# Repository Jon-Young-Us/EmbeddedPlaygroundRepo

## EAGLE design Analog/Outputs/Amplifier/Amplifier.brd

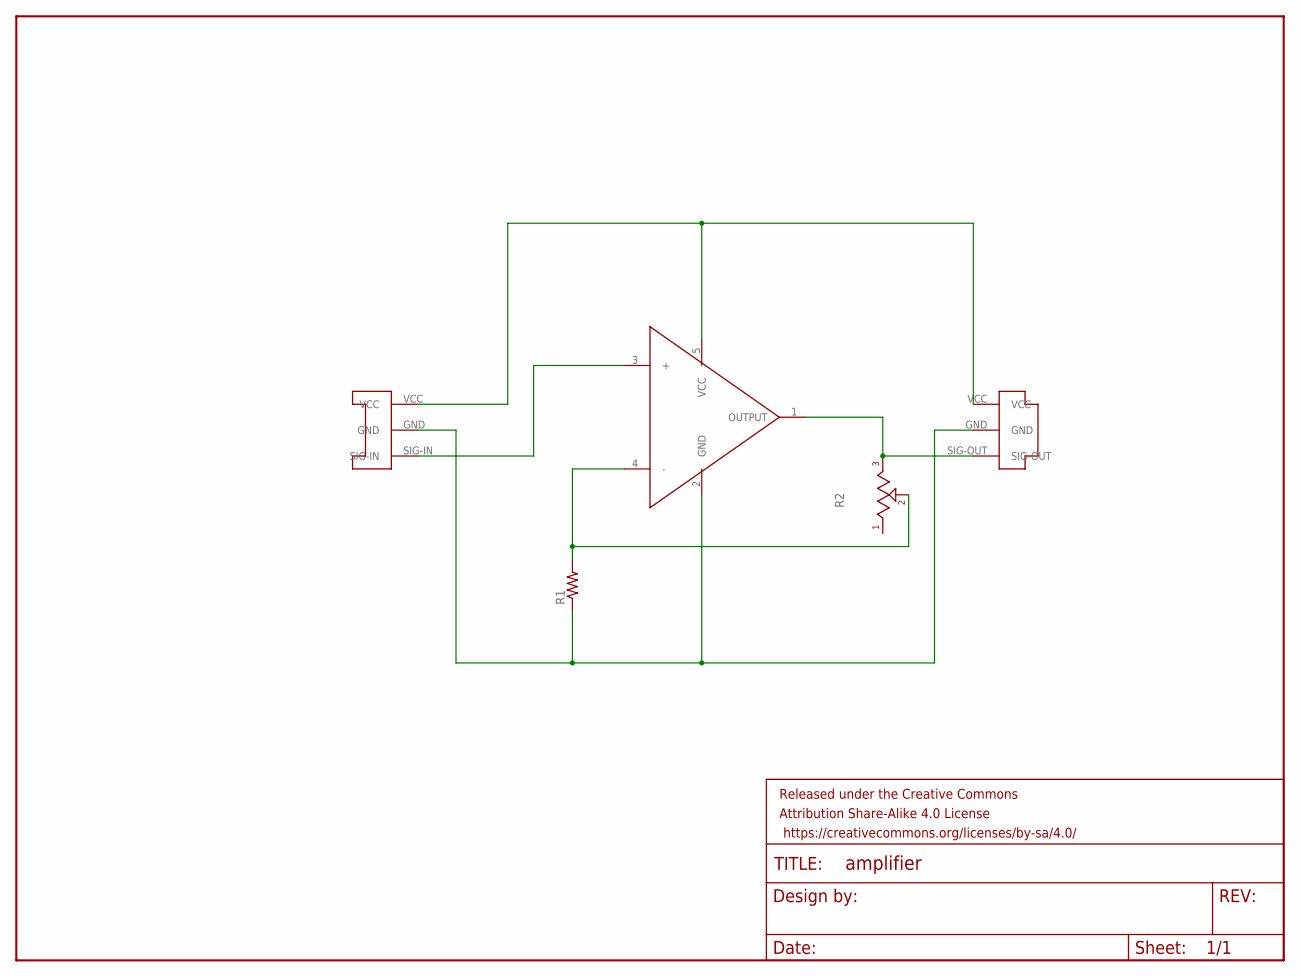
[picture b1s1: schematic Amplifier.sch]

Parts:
FRAME1: FRAME-LETTERNO_PACKAGE; DUMMY
R1: RESISTOR0603; 0603-RES
R2: POT-TRIM-SMD-BOURNS-3314J-1; POT-TRIM-SMD-BOURNS-3314
U$1: CONN-PLUG-3POS-3MM; PLUG-3POS-3MM-SMD
U$2: CONN-SOCKET-3POS-3MM; SOCKET-3POS-3MM-SMD
U$3: OPAMP-MCP6001SC70-5; SC70

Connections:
GND: R1.1, U$1.GND, U$2.GND, U$3.2 (GND)
unnamed: U$2.SIG-IN, U$3.3 (+)
unnamed: R1.2, R2.2, U$3.4 (-)
unnamed: R2.1 (3), U$1.SIG-OUT, U$3.1 (OUTPUT)
VCC: U$1.VCC, U$2.VCC, U$3.5 (VCC)

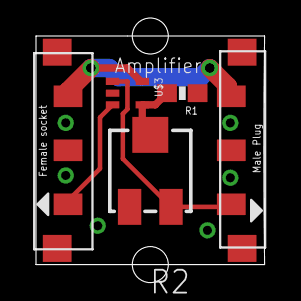
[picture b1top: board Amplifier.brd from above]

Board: 2 copper layers, 12.7 x 12.7 mm, 6 parts (0 on the bottom side), 5 nets.

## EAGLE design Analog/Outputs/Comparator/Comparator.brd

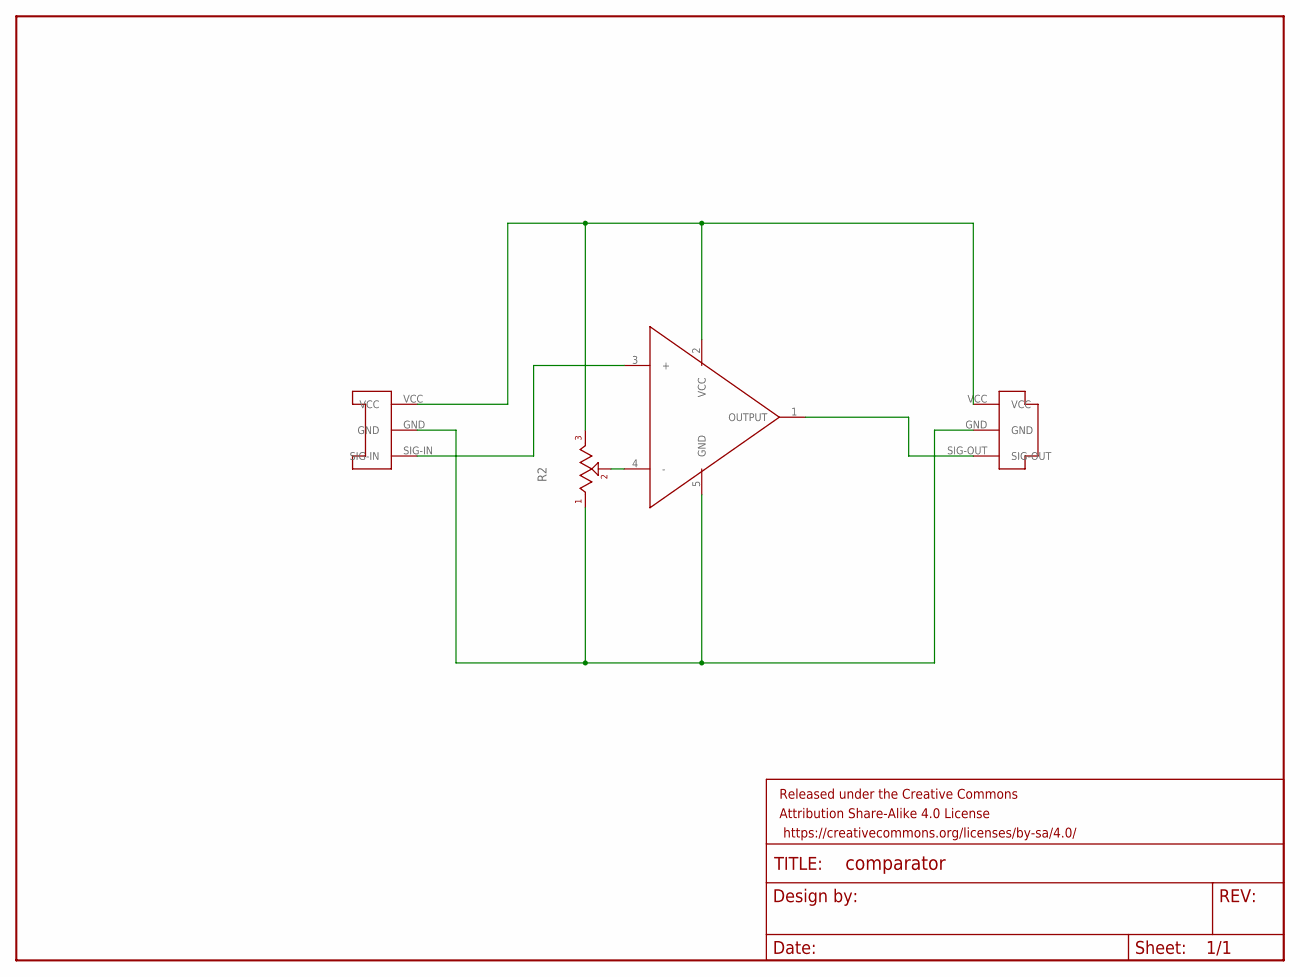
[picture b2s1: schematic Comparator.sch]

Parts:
FRAME1: FRAME-LETTERNO_PACKAGE; DUMMY
R2: POT-TRIM-SMD-BOURNS-3314J-1; POT-TRIM-SMD-BOURNS-3314
U$1: CONN-PLUG-3POS-3MM; PLUG-3POS-3MM-SMD
U$2: CONN-SOCKET-3POS-3MM; SOCKET-3POS-3MM-SMD
U$3: COMPARATOR-NCS2200; SOT23-5

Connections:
GND: R2.3 (1), U$1.GND, U$2.GND, U$3.5 (GND)
unnamed: U$2.SIG-IN, U$3.3 (+)
unnamed: R2.2, U$3.4 (-)
unnamed: U$1.SIG-OUT, U$3.1 (OUTPUT)
VCC: R2.1 (3), U$1.VCC, U$2.VCC, U$3.2 (VCC)

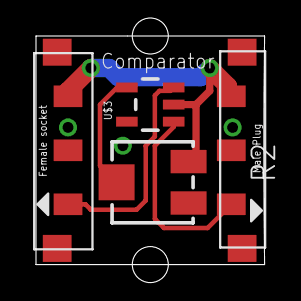
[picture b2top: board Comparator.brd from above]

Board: 2 copper layers, 12.7 x 12.7 mm, 5 parts (0 on the bottom side), 5 nets.

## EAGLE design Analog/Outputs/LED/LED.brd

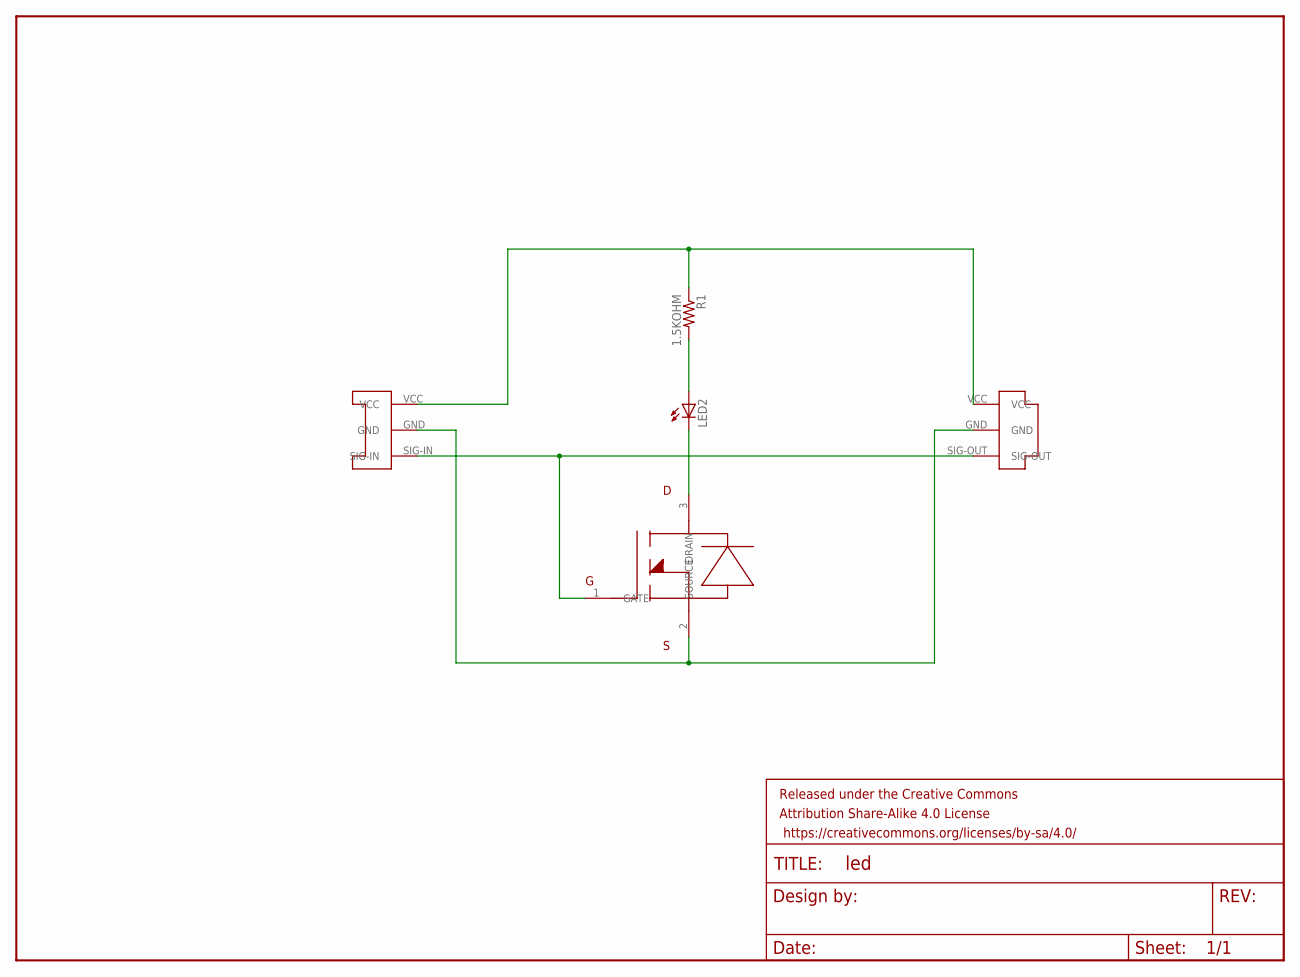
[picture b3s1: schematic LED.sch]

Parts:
FRAME1: FRAME-LETTERNO_PACKAGE; DUMMY
LED2: LEDCHIPLED_1206; CHIPLED_1206
R1: 1.5KOHM; 0603
U$1: CONN-PLUG-3POS-3MM; PLUG-3POS-3MM-SMD
U$2: CONN-SOCKET-3POS-3MM; SOCKET-3POS-3MM-SMD
U$3: MOSFET-N-CHAN; SOT23-3

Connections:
GND: U$1.GND, U$2.GND, U$3.2 (SOURCE)
unnamed: LED2.A, R1.2
unnamed: LED2.C, U$3.3 (DRAIN)
SIG: U$1.SIG-OUT, U$2.SIG-IN, U$3.1 (GATE)
VCC: R1.1, U$1.VCC, U$2.VCC

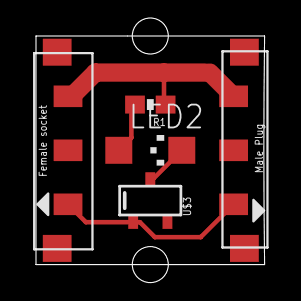
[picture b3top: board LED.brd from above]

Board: 2 copper layers, 12.7 x 12.7 mm, 6 parts (0 on the bottom side), 5 nets.

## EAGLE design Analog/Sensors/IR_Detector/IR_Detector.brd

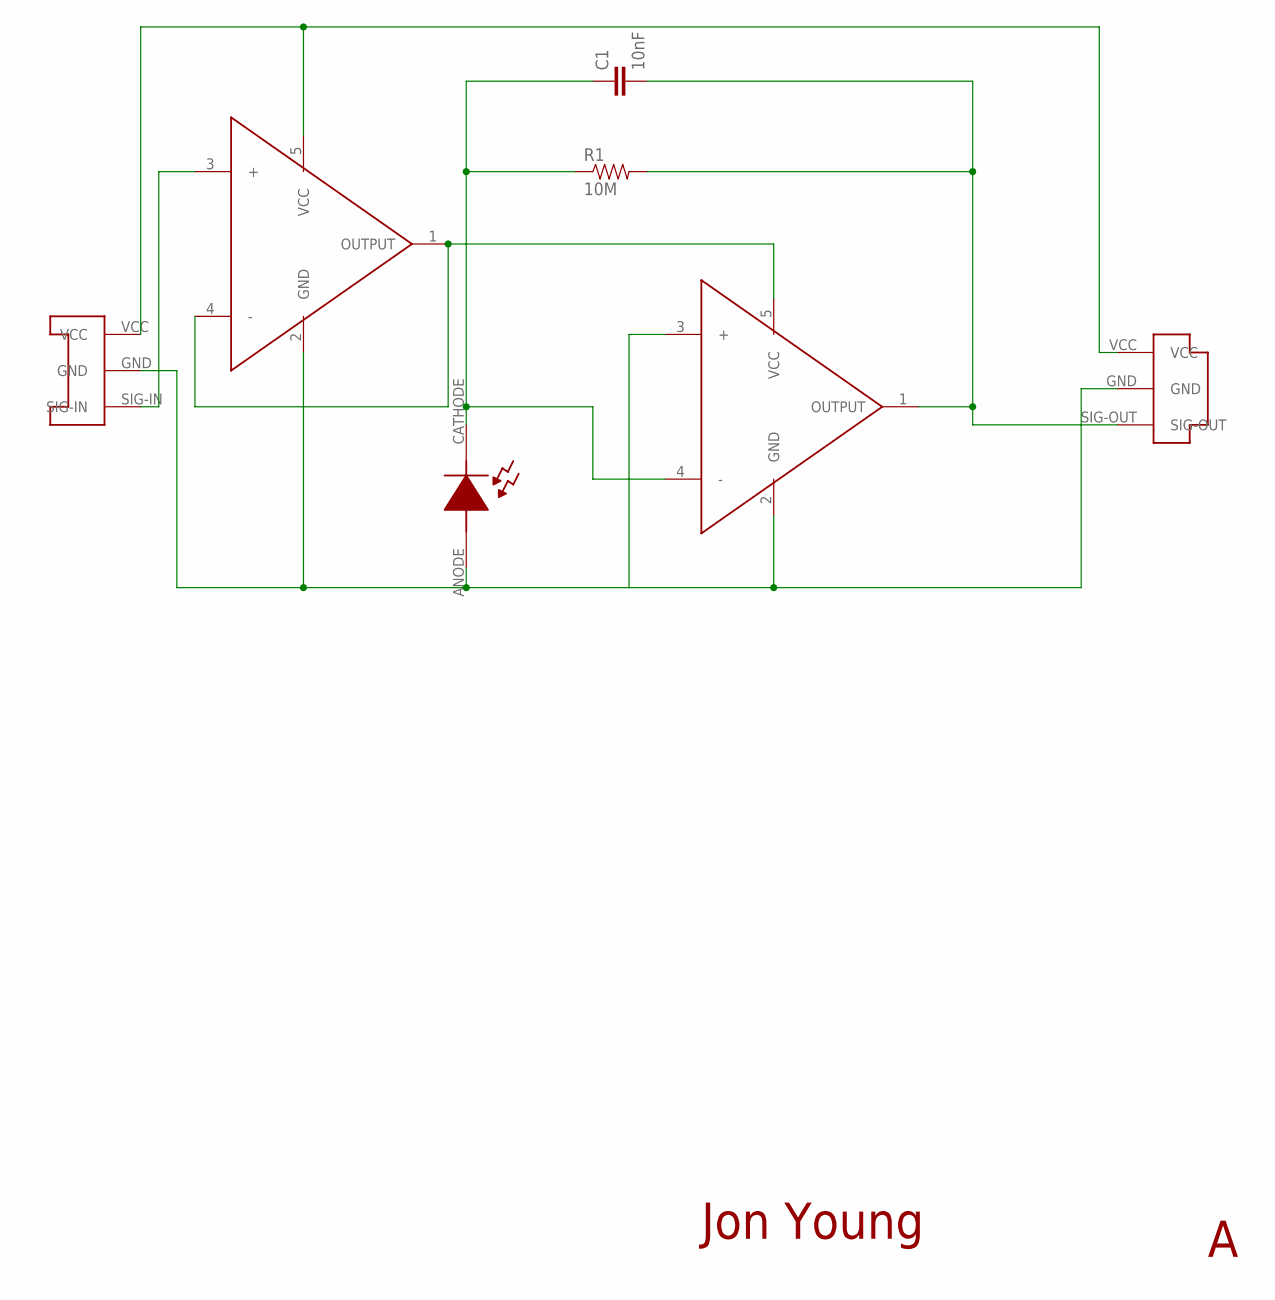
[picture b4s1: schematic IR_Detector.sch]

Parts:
C1: 10nF; 0603-CAP
R1: 10M; 0603-RES
U$1: CONN-PLUG-3POS-3MM; PLUG-3POS-3MM-SMD
U$2: CONN-SOCKET-3POS-3MM; SOCKET-3POS-3MM-SMD
U$3: VEMD2020; VEMD2020X01
U$4, U$5: OPAMP-MCP6001SC70-5; SC70

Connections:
GND: U$1.GND, U$2.GND, U$3.ANODE, U$4.2 (GND), U$4.3 (+), U$5.2 (GND)
unnamed: U$2.SIG-IN, U$5.3 (+)
unnamed: C1.1, R1.1, U$3.CATHODE, U$4.4 (-)
unnamed: U$4.5 (VCC), U$5.1 (OUTPUT), U$5.4 (-)
SIG-OUT: C1.2, R1.2, U$1.SIG-OUT, U$4.1 (OUTPUT)
VCC: U$1.VCC, U$2.VCC, U$5.5 (VCC)

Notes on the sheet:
Jon Young

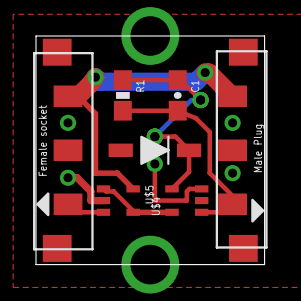
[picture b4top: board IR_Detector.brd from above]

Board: 2 copper layers, 12.7 x 12.7 mm, 7 parts (0 on the bottom side), 6 nets.

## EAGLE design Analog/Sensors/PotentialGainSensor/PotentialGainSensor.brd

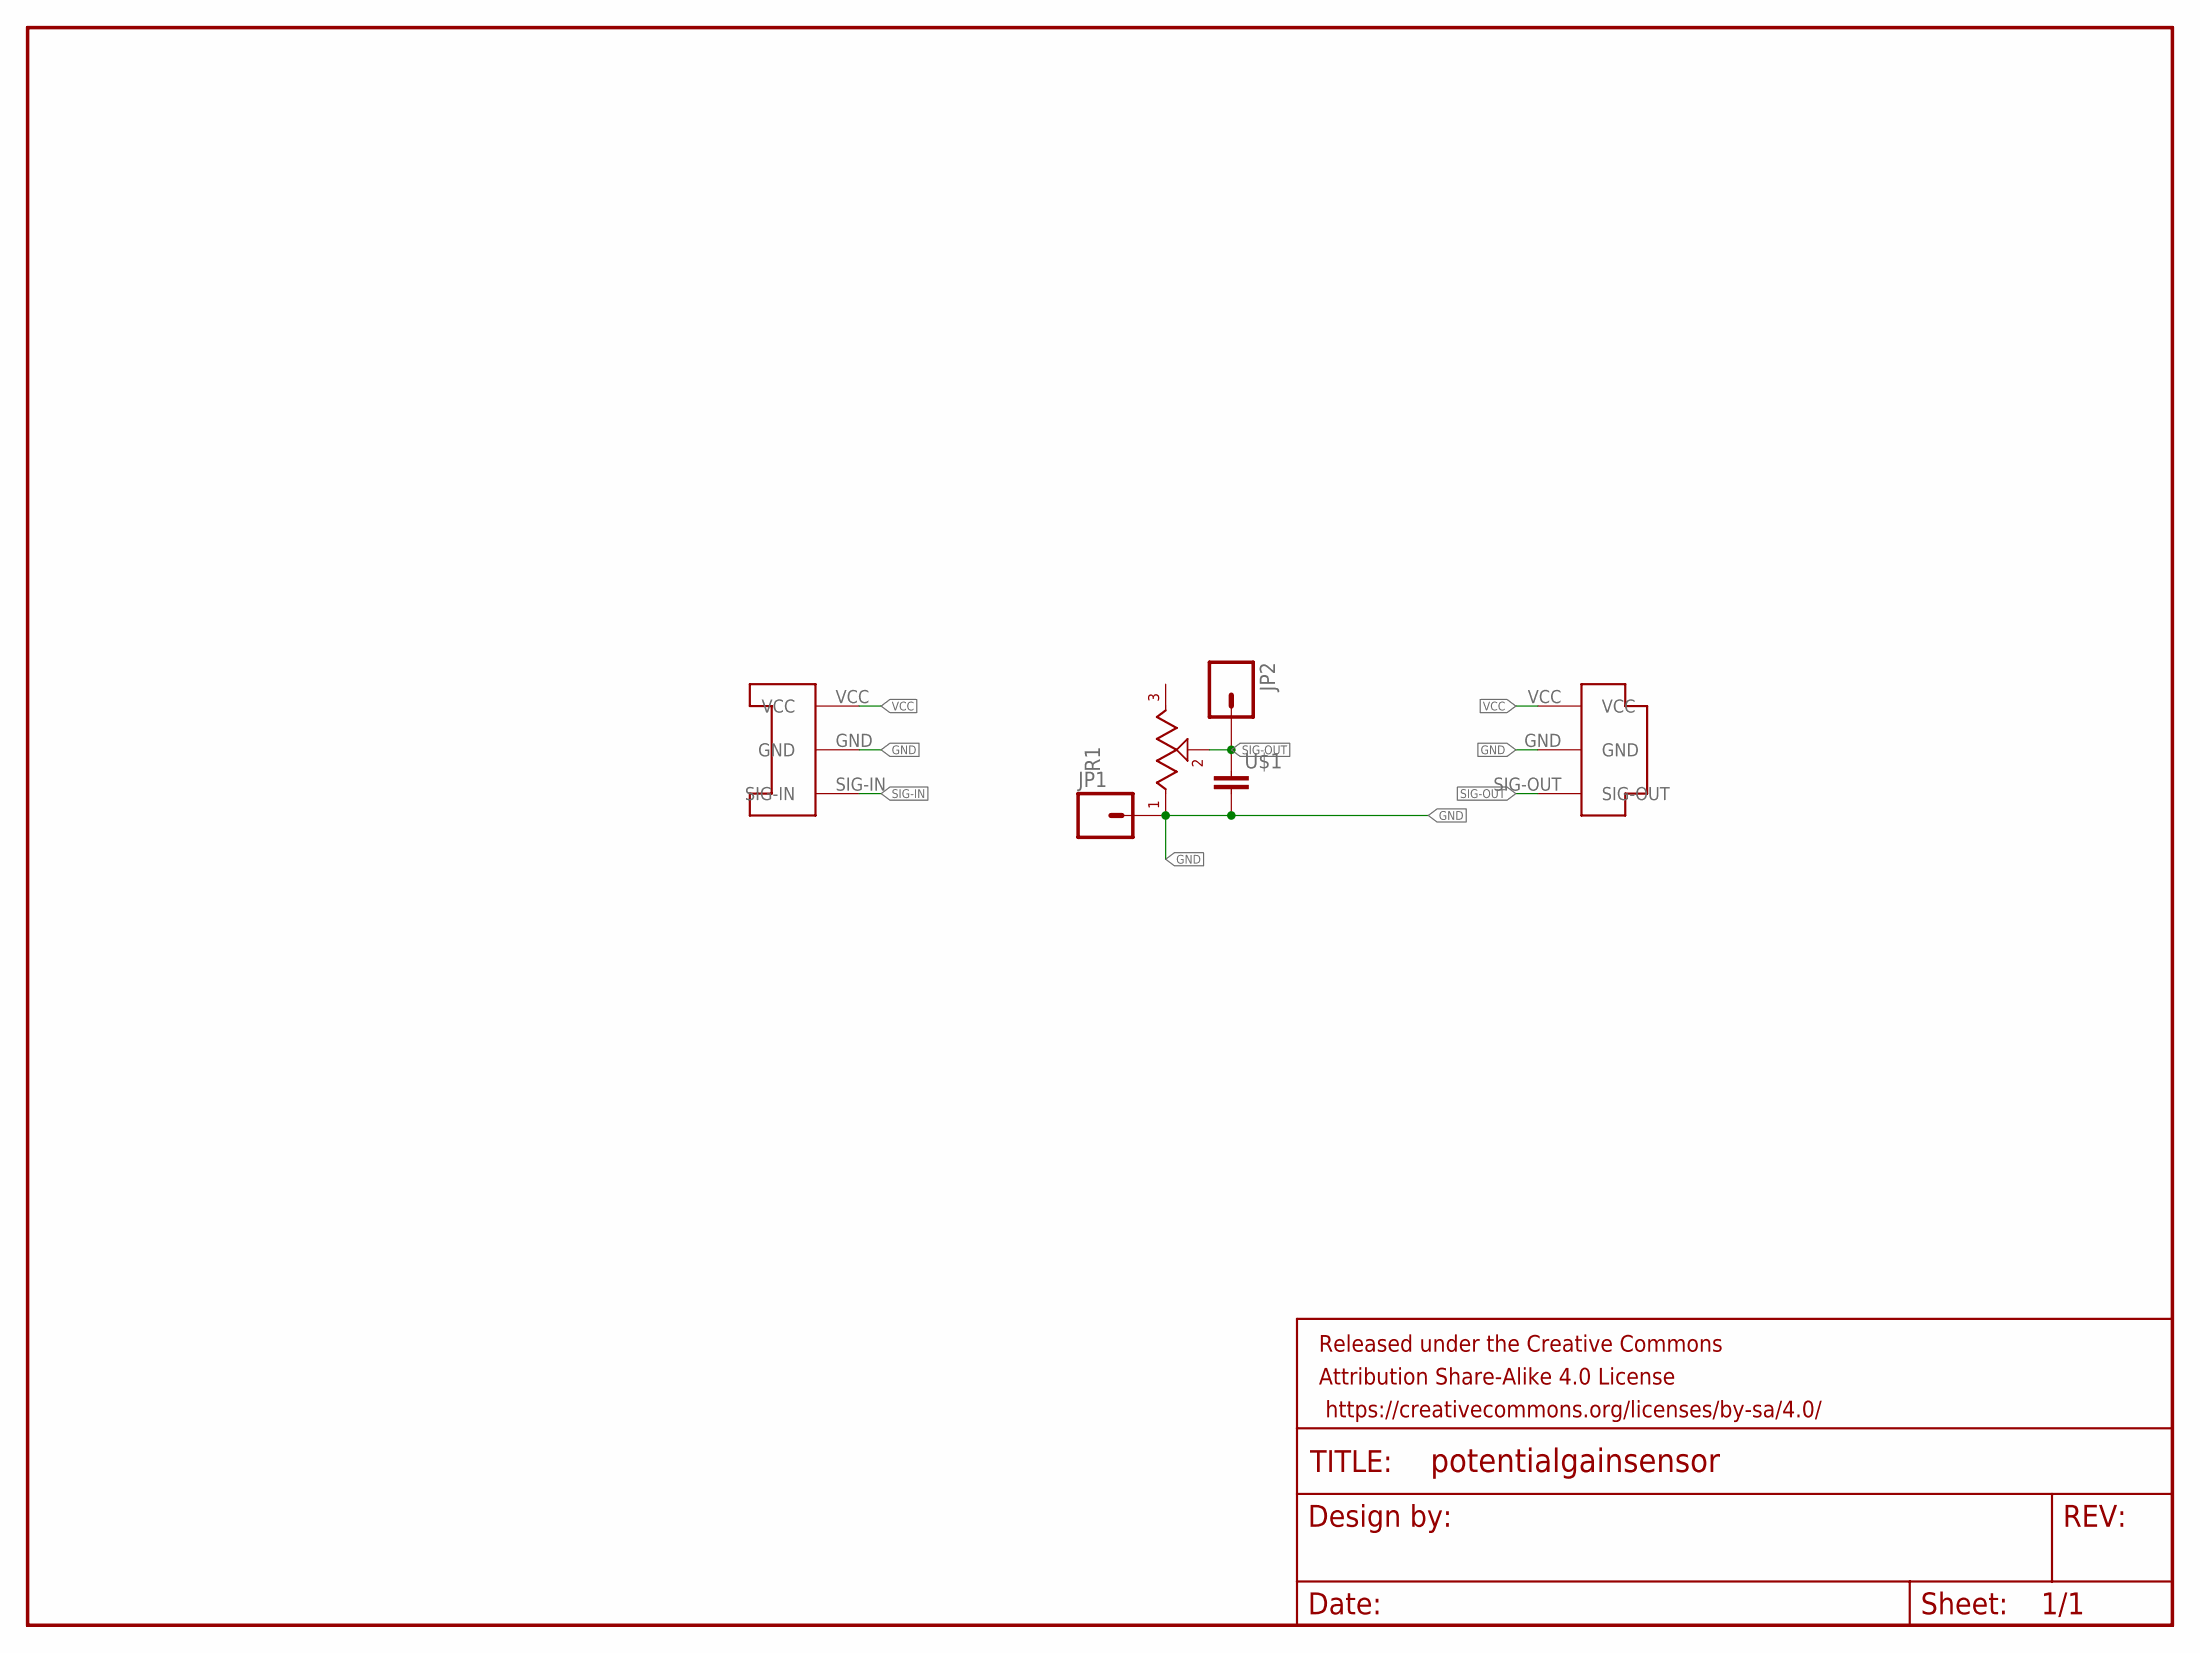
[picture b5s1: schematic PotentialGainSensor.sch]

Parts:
FRAME1: FRAME-LETTERNO_PACKAGE; DUMMY
JP1, JP2: M01SPRING-CONN; SPRING-CONNECTOR
R1: POT-TRIM-SMD-BOURNS-3314J-1; POT-TRIM-SMD-BOURNS-3314
U$1: CAPCAP-0805; CAP-0805
U$2: CONN-PLUG-3POS-3MM; PLUG-3POS-3MM-SMD
U$3: CONN-SOCKET-3POS-3MM; SOCKET-3POS-3MM-SMD

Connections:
GND: JP1.P$2, R1.3 (1), U$1.2, U$2.GND, U$3.GND
SIG-IN: U$3.SIG-IN
SIG-OUT: JP2.P$2, R1.2, U$1.1, U$2.SIG-OUT
VCC: U$2.VCC, U$3.VCC

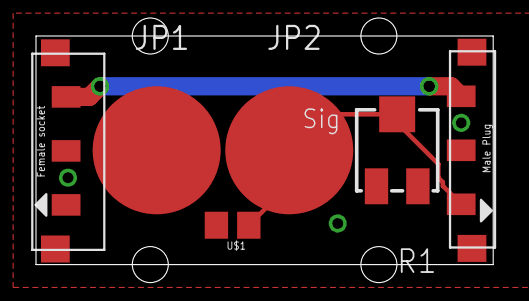
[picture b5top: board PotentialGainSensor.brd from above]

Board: 2 copper layers, 25.4 x 12.7 mm, 7 parts (0 on the bottom side), 3 nets.

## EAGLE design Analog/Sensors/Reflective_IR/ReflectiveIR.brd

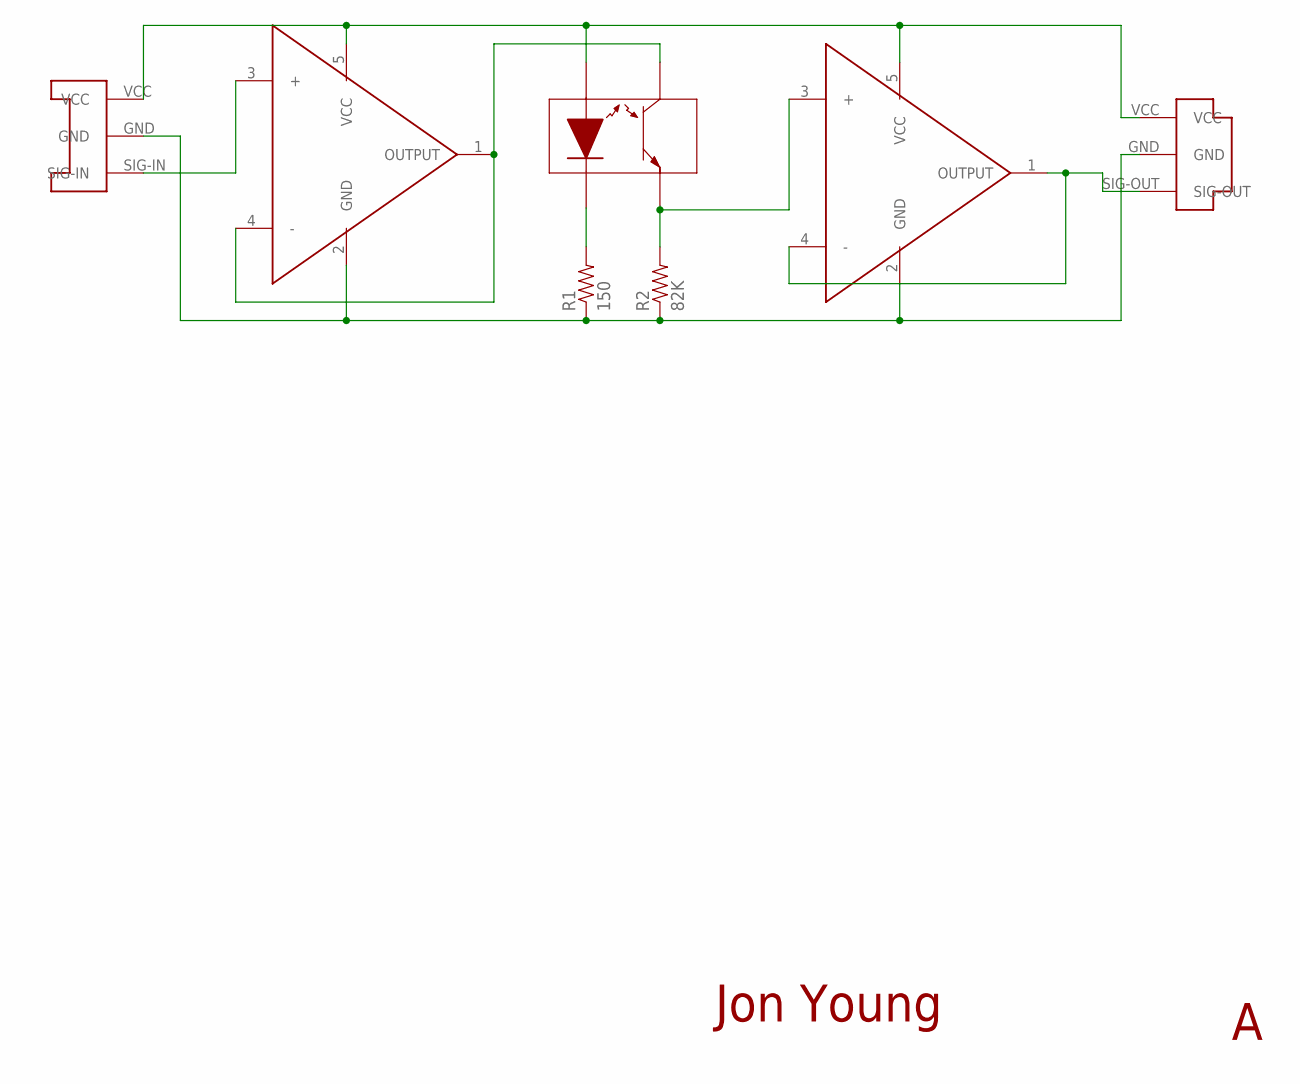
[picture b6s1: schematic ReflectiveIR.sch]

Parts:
R1: 150; 0603-RES
R2: 82K; 0603-RES
U$1: CONN-PLUG-3POS-3MM; PLUG-3POS-3MM-SMD
U$2: CONN-SOCKET-3POS-3MM; SOCKET-3POS-3MM-SMD
U$3: REFLECTIVE-SENSOR-OPB733TR
U$4, U$5: OPAMP-MCP6001SC70-5; SC70

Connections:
GND: R1.1, R2.1, U$1.GND, U$2.GND, U$4.2 (GND), U$5.2 (GND)
unnamed: R2.2, U$3.P2-EMITTER, U$5.3 (+)
unnamed: R1.2, U$3.P1-CATHODE
unnamed: U$3.P3-COLLECTOR, U$4.1 (OUTPUT), U$4.4 (-)
unnamed: U$2.SIG-IN, U$4.3 (+)
SIG-OUT: U$1.SIG-OUT, U$5.1 (OUTPUT), U$5.4 (-)
VCC: U$1.VCC, U$2.VCC, U$3.P4-ANODE, U$4.5 (VCC), U$5.5 (VCC)

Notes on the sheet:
Jon Young

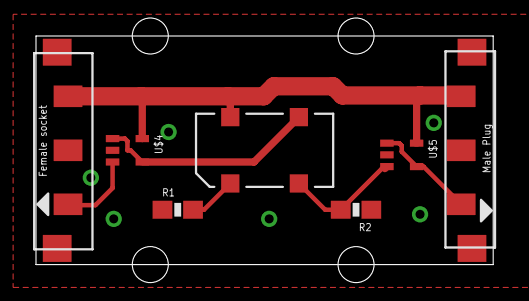
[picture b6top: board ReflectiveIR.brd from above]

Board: 2 copper layers, 25.4 x 12.7 mm, 7 parts (0 on the bottom side), 7 nets.

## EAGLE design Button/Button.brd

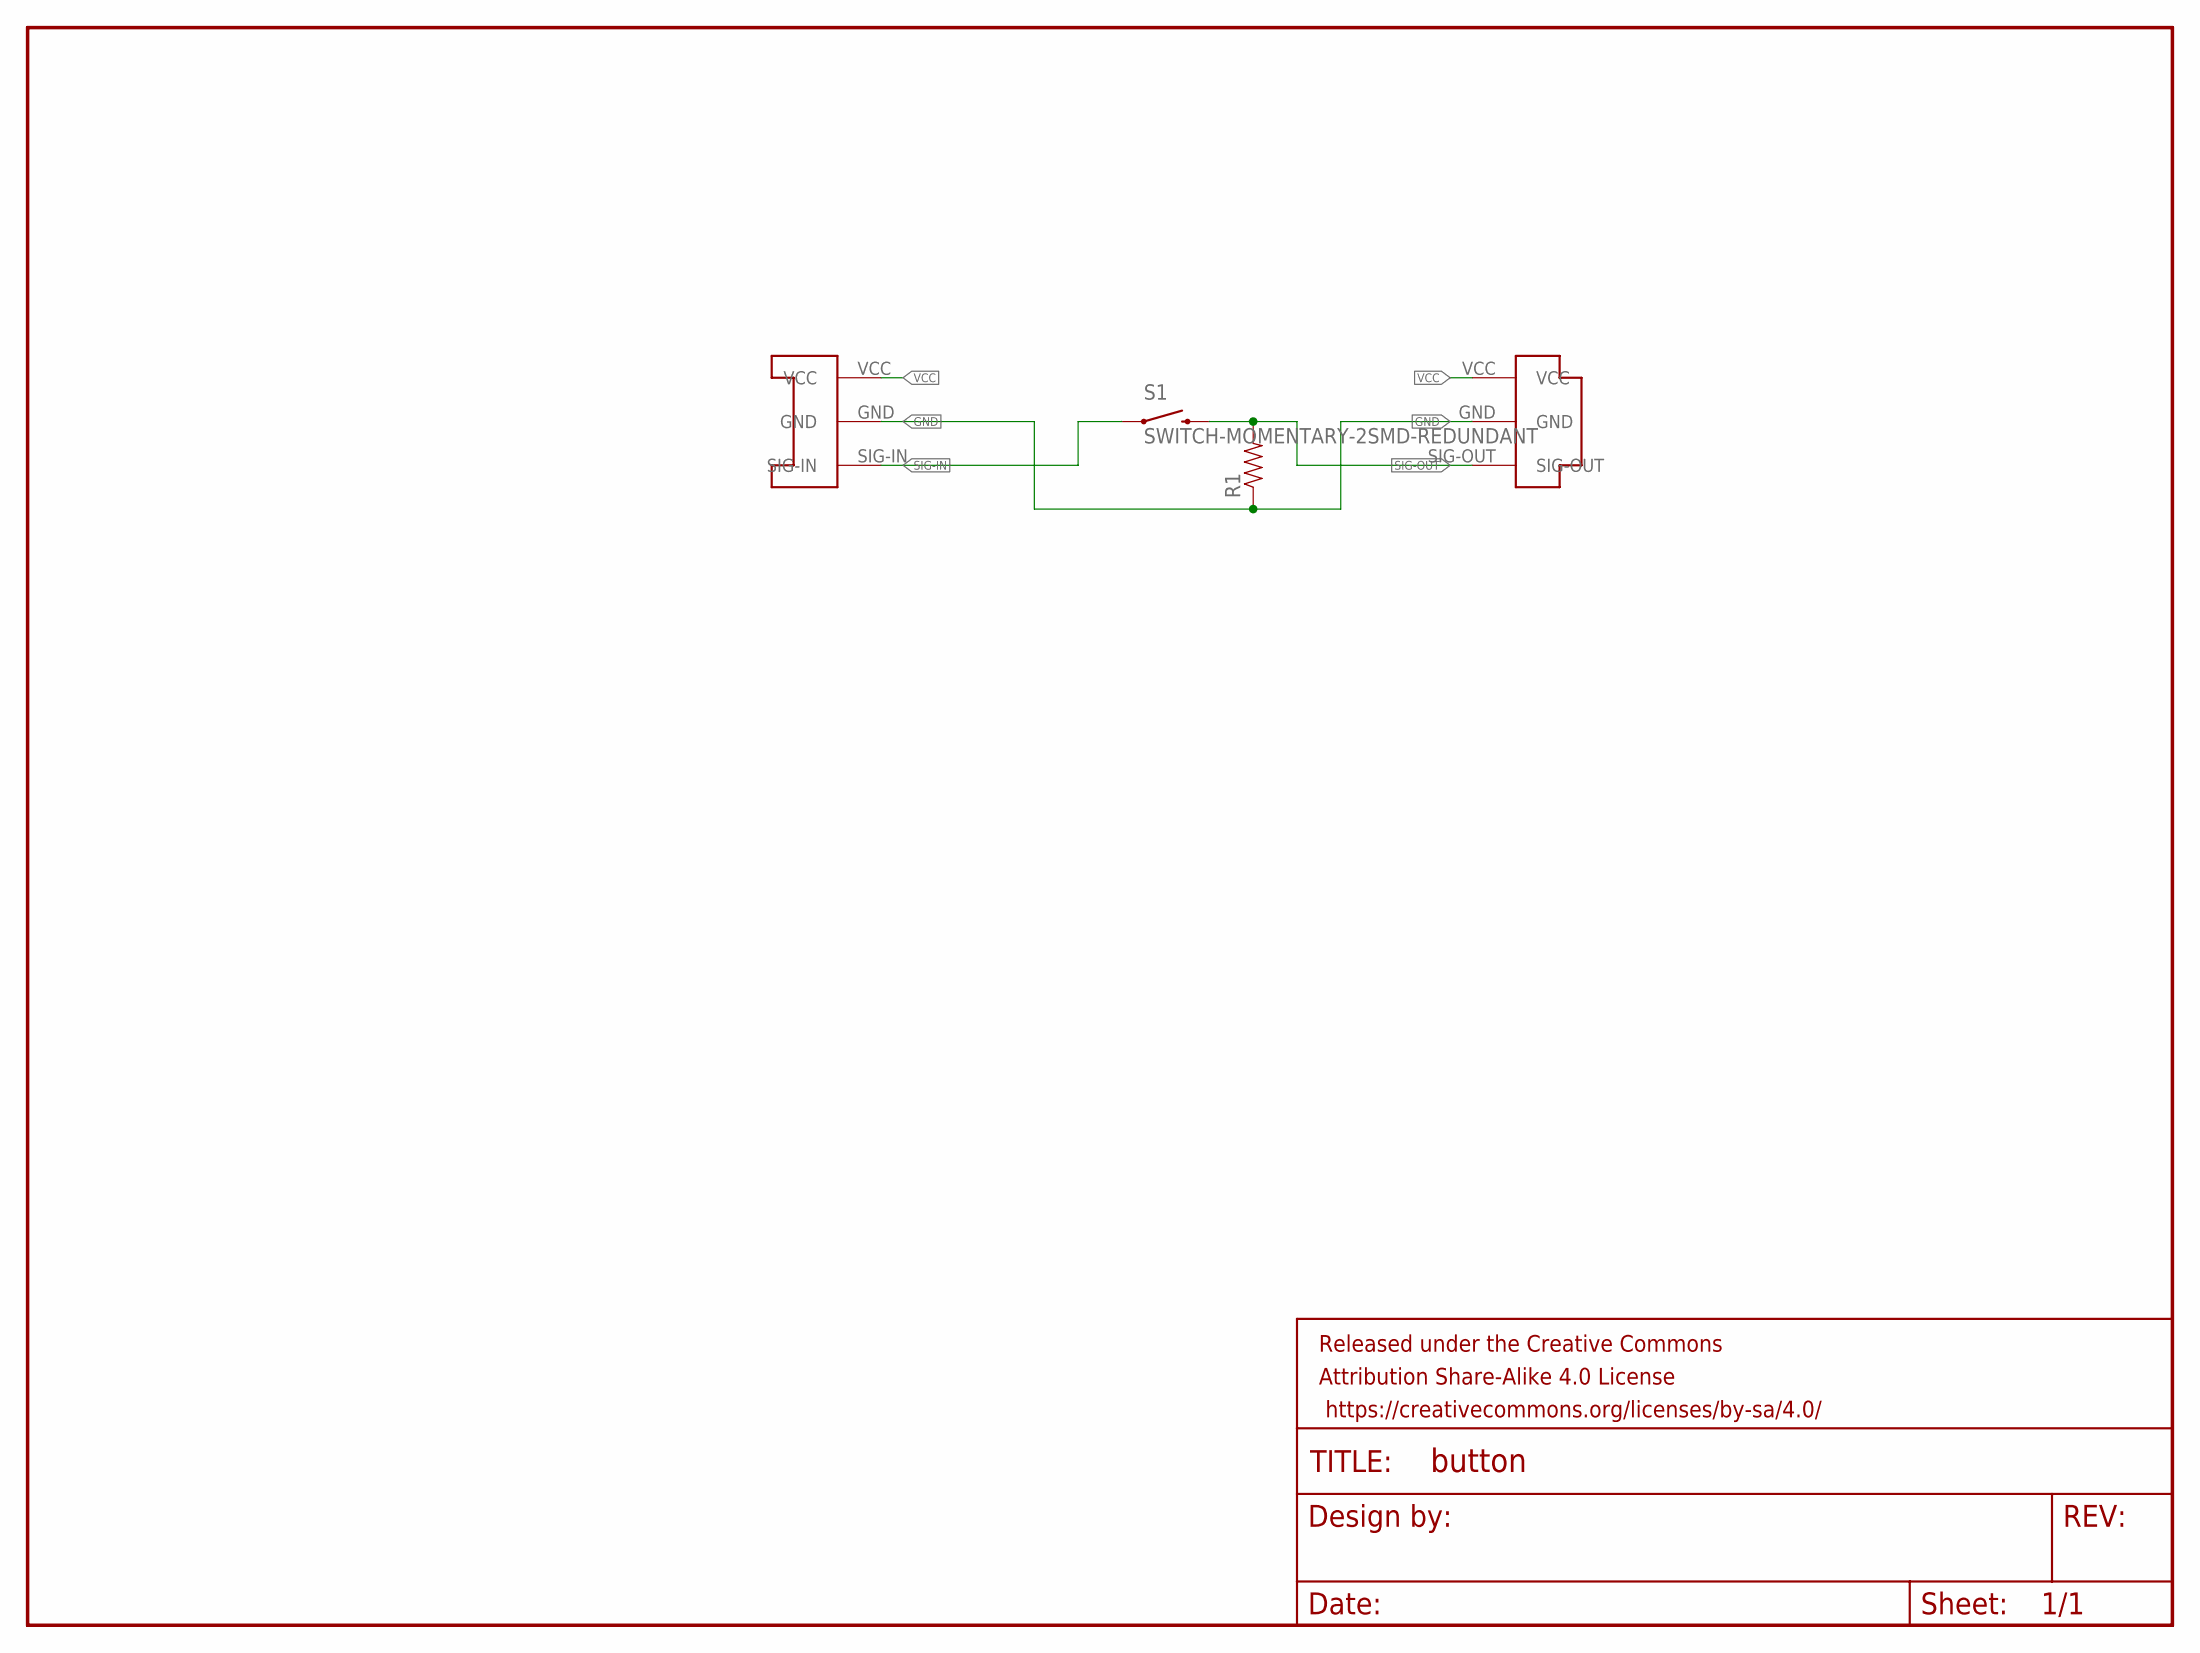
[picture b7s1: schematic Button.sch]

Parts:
FRAME1: FRAME-LETTERNO_PACKAGE; DUMMY
R1: RESISTOR0603; 0603-RES
S1: SWITCH-MOMENTARY-2SMD-REDUNDANT; TACTILE-SWITCH-SMD
U$1: CONN-PLUG-3POS-3MM; PLUG-3POS-3MM-SMD
U$2: CONN-SOCKET-3POS-3MM; SOCKET-3POS-3MM-SMD

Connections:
GND: R1.1, U$1.GND, U$2.GND
SIG-IN: S1.1, S1.2 (1), U$2.SIG-IN
SIG-OUT: R1.2, S1.3 (2), S1.4 (2), U$1.SIG-OUT
VCC: U$1.VCC, U$2.VCC

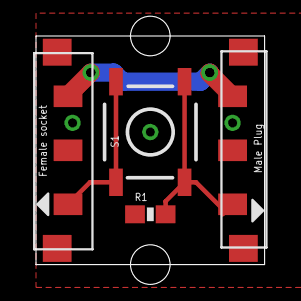
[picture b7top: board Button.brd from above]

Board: 2 copper layers, 12.7 x 12.7 mm, 5 parts (0 on the bottom side), 4 nets.

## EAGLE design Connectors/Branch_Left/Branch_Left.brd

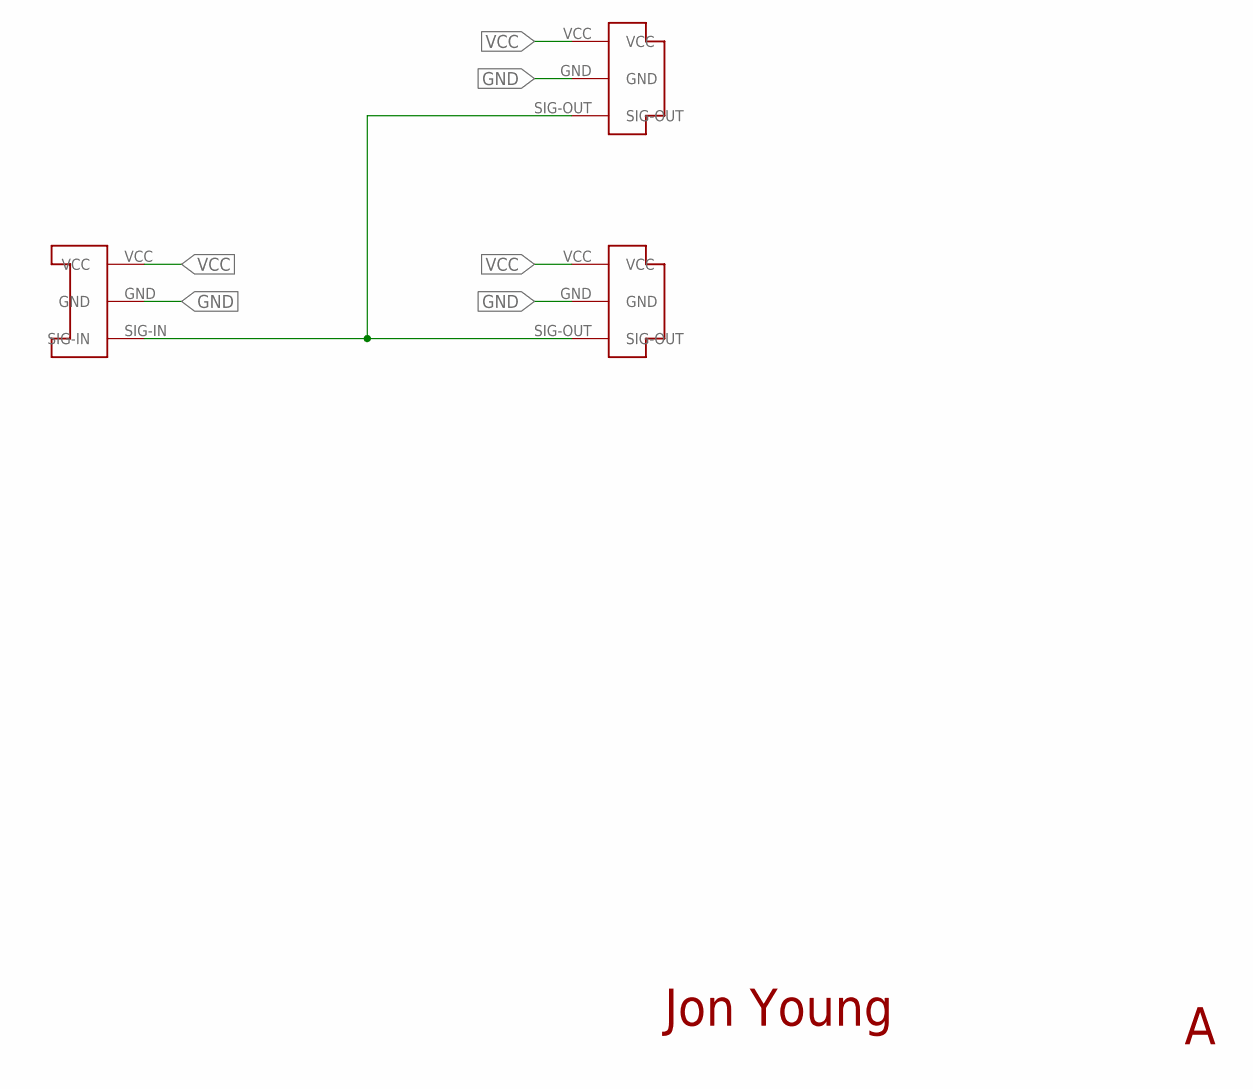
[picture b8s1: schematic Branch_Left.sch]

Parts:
U$1, U$4: CONN-PLUG-3POS-3MM; PLUG-3POS-3MM-SMD
U$2: CONN-SOCKET-3POS-3MM; SOCKET-3POS-3MM-SMD

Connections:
GND: U$1.GND, U$2.GND, U$4.GND
VCC: U$1.VCC, U$2.VCC, U$4.VCC
Y: U$1.SIG-OUT, U$2.SIG-IN, U$4.SIG-OUT

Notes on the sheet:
Jon Young

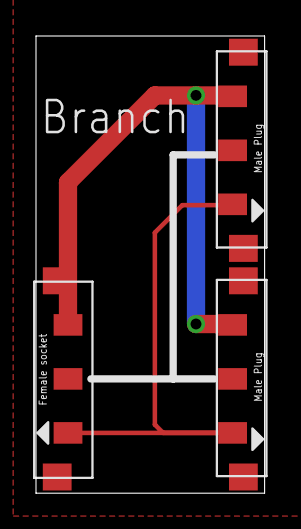
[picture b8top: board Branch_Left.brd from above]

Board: 2 copper layers, 12.7 x 25.4 mm, 3 parts (0 on the bottom side), 3 nets.

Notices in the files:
parts and their libraries:
SparkFun-Aesthetics: Licensing: Creative Commons ShareAlike 4.0 International - https://creativecommons.org/licenses/by-sa/4.0
SparkFun-Aesthetics: Released under the Creative Commons Attribution Share-Alike 4.0 License
SparkFun-Aesthetics: https://creativecommons.org/licenses/by-sa/4.0
